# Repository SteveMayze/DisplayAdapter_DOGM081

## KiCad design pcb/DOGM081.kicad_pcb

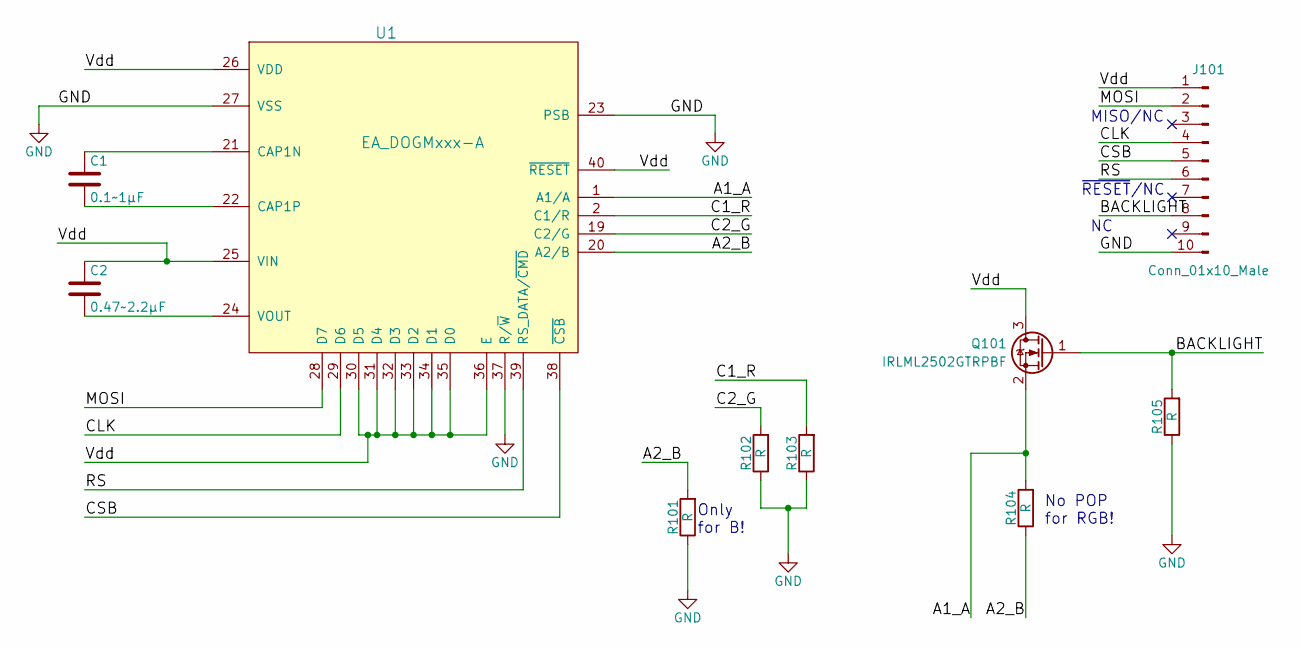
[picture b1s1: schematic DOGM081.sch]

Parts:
C1: 0.1~~1μF; C_1206_HandSoldering
C2: 0.47~~2.2μF; C_1206_HandSoldering
J101: Conn_01x10_Male; Pin_Header_Straight_1x10_Pitch2.54mm
Q101: IRLML2502GTRPBF; SOT-23; MPN IRLML2502GTRPBF
R101, R102, R103, R104, R105: R; R_0805_HandSoldering
U1: EA_DOGMxxx-A; EA_DOGM081x-A

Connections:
/A1_A: Q101.2 (S), R104.2, U1.1 (A1/A)
/A2_B: R101.2, R104.1, U1.20 (A2/B)
/BACKLIGHT: J101.8, Q101.1 (G), R105.2
/C1_R: R103.2, U1.2 (C1/R)
/C2_G: R102.2, U1.19 (C2/G)
/CLK: J101.4, U1.29 (D6)
/CSB: J101.5, U1.38 (~CSB)
/MOSI: J101.2, U1.28 (D7)
/RS: J101.6, U1.39 (RS_DATA/~CMD)
/Vdd: C2.1, J101.1, Q101.3 (D), U1.25 (VIN), U1.26 (VDD), U1.30 (D5), U1.31 (D4), U1.32 (D3), U1.33 (D2), U1.34 (D1), U1.35 (D0), U1.36 (E), U1.40 (~RESET)
GND: J101.10, R101.1, R102.1, R103.1, R105.1, U1.23 (PSB), U1.27 (VSS), U1.37 (R/~W)
unnamed: C1.1, U1.21 (CAP1N)
unnamed: C1.2, U1.22 (CAP1P)
unnamed: C2.2, U1.24 (VOUT)

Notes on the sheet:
No POP for RGB!
MISO/NC
Only for B!
~RESET~/NC

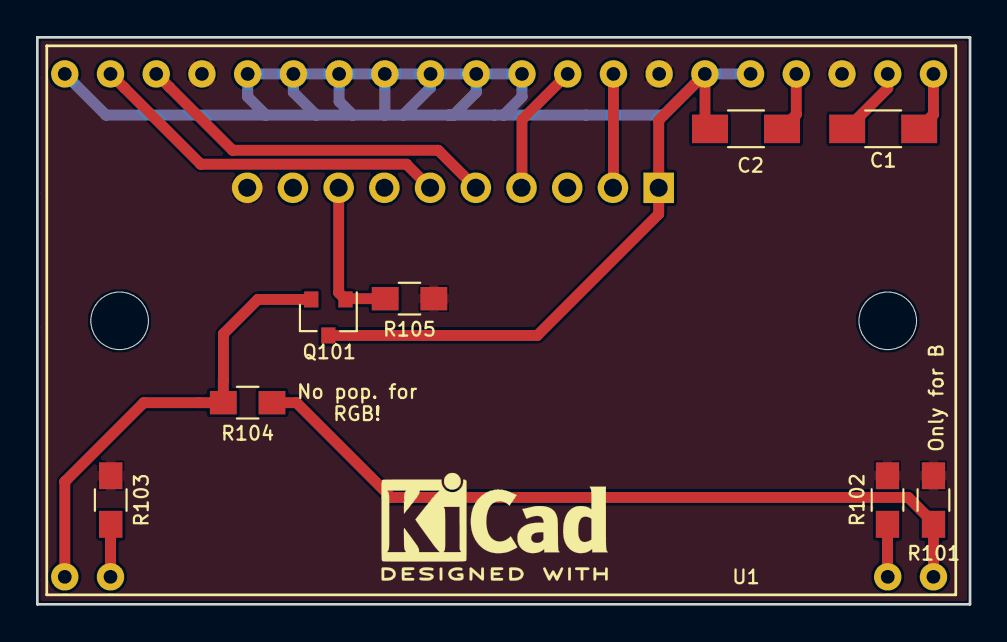
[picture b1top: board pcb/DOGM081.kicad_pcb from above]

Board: 2 copper layers, 51.8 x 31.5 mm, 12 parts (1 on the bottom side), 14 nets.

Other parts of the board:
MNT**: MountingHole_3.2mm_M3
MNT**#2: MountingHole_3.2mm_M3

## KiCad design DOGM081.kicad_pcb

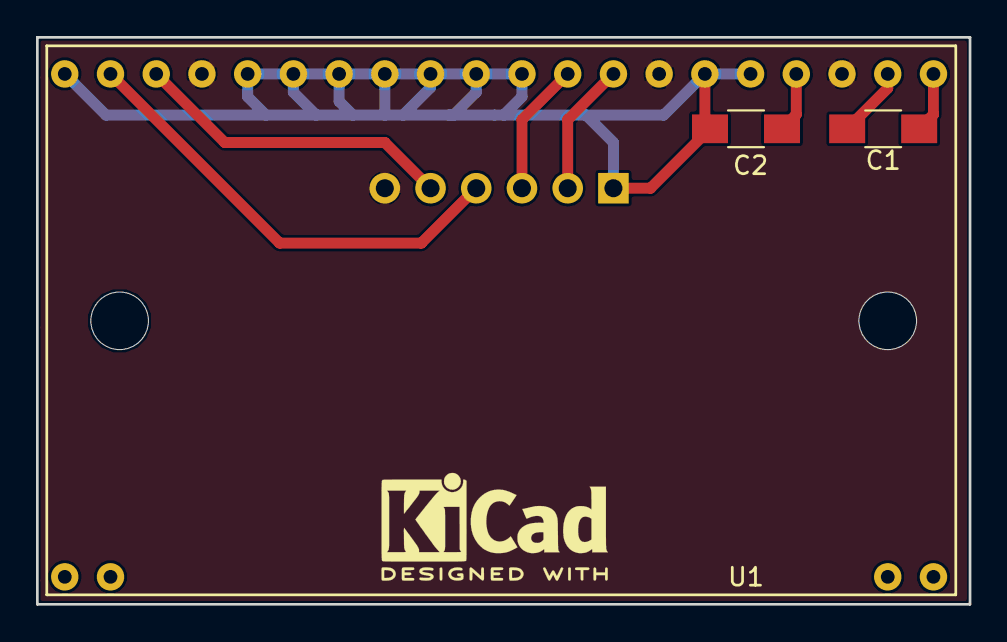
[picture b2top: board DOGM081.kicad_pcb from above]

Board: 2 copper layers, 51.8 x 31.5 mm, 6 parts (1 on the bottom side), 9 nets.

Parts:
C1: 0.1~~1μF; C_1206_HandSoldering
C2: 0.47~~2.2μF; C_1206_HandSoldering
MNT**: MountingHole_3.2mm_M3
MNT**#2: MountingHole_3.2mm_M3
P1: CONN_01X06; Socket_Strip_Straight_1x06_Pitch2.54mm
U1: EA_DOGMxxx-A; EA_DOGM081x-A

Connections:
/CLK: P1.3, U1.29
/CSB: P1.5, U1.38
/MOSI: P1.2, U1.28
/RS: P1.4, U1.39
/Vdd: C2.1, P1.1, U1.25, U1.26, U1.30, U1.31, U1.32, U1.33, U1.34, U1.35, U1.36, U1.40
GND: P1.6, U1.23, U1.27, U1.37
unnamed: C1.1, U1.21
unnamed: C1.2, U1.22
unnamed: C2.2, U1.24

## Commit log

2017-08-08 Initial checkin with the DOGM081WA symbol
2017-08-09 Layout completed and sent to OSH Park
2018-01-10 Migrated the arduino example from the field device
2018-01-26 Started the revision 2 to support a backlight and a generic connector
2018-01-27 Complted the Rev2 layout and sent to OSHPark. Feature for back-light
